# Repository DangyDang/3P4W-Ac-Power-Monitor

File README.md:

I dropped the project lol :( 
My firmware worked but it nothing compare to a dedicated IC for power monitoring.

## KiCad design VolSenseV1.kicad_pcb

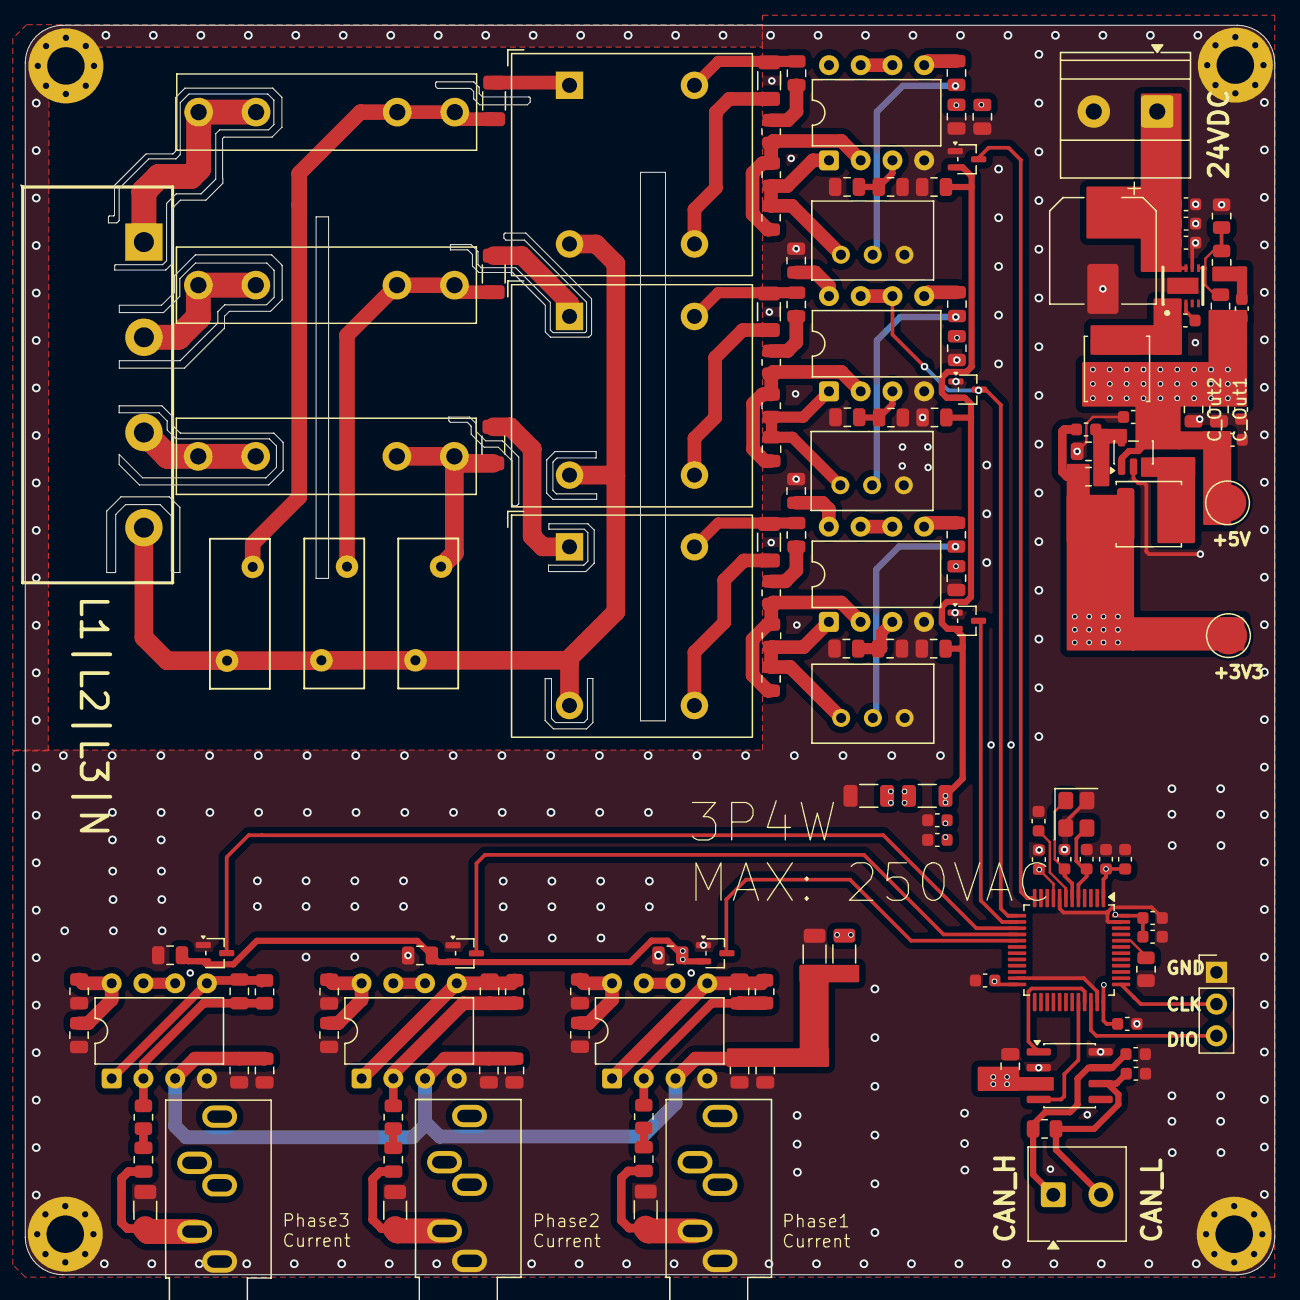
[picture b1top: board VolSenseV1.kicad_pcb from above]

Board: 4 copper layers, 100.0 x 100.0 mm, 148 parts (0 on the bottom side), 76 nets.

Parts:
C1, C2, C3, C4, C5, C6, C7, C8, C39, C43, C63: 100n; C_0603_1608Metric
C9, C10: 22p; C_0603_1608Metric
C11, C15, C19, C23, C28, C33: DNI; C_0805_2012Metric
C12, C13, C14, C16, C17, C18, C20, C21, C22, C24, C25, C26, C27, C29, C30, C31, C32, C34, C35, C36, C37, C44, C45, C47, C48, C50, C51, C57, C58, C59, C60, C61, C62: C; C_0805_2012Metric
C38: 100u; CP_Elec_8x6.2
C40: NC; C_0603_1608Metric
C41, C42: 10u; C_0603_1608Metric
C46, C49, C52, C53, C54, C55, C56: 100n; C_0805_2012Metric
C64, C65: 33pf; C_0603_1608Metric
C_FF1: 33p; C_0603_1608Metric
C_IN1, C_IN2: 4u7; C_0603_1608Metric
C_Out1, C_Out2: 33u; C_0805_2012Metric
C_boot1: 100nf; C_0603_1608Metric
Cin_HF1: 100n; C_0603_1608Metric
D1, D2, D3, D4, D5, D6: BAT54SW; SOT-323_SC-70
F1, F2, F3: Fuse; Fuseholder_Littelfuse_100_series_5x20mm
H1, H2, H3, H4: MountingHole_Pad; MountingHole_3mm_Pad_Via
J1: Conn_01x02; TerminalBlock_Phoenix_MKDS-1-2-3.81_1x02_P3.81mm_Horizontal
J2: Conn_01x03; PinHeader_1x03_P2.54mm_Vertical
J3, J4, J5: AudioJack4; Jack_3.5mm_CUI_SJ1-3535NG_Horizontal
J6: POWER INPUT; TerminalBlock_Phoenix_MKDS-1,5-2-5.08_1x02_P5.08mm_Horizont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
L1: 5u6; L_Sunlord_SWPA5020S
L2: 2u2; L_Sunlord_SWPA5020S
R1: 120; R_0805_2012Metric
R2, R3, R5, R6, R10, R11, R13, R15, R17, R19, R21, R23, R29: R; R_0805_2012Metric
R4, R7, R8, R9, R12, R27, R28: R; R_1206_3216Metric
R14, R18, R22: 820k; R_1206_3216Metric
R16, R20, R24: 100; R_1206_3216Metric
R25: 68k; R_0805_2012Metric
R26: 15k; R_0805_2012Metric
RV1, RV3, RV5: 275 VAC; RV_Disc_D12mm_W4.8mm_P7.5mm
RV2, RV4, RV6: R_Potentiometer; Potentiometer_Bourns_3299W_Vertical
R_FBB1: 19k1; R_0805_2012Metric
R_FBT1: 100k; R_0805_2012Metric
R_FF1: 1k; R_0805_2012Metric
TP1, TP2: TestPoint; TestPoint_Pad_D3.0mm
TR1, TR2, TR3: ZMPT101K; Transformer_Zeming_ZMPT101K
U1: STM32F103C8Tx; LQFP-48_7x7mm_P0.5mm
U2: TJA1051T; SOIC-8_3.9x4.9mm_P1.27mm
U3, U4, U5, U6, U8, U9: MCP6002-xP; DIP-8_W7.62mm
U7: KF7.62-4P; C707826_CONN-TH_KF7_62-4P
U10: LMR51450SDRRR; C6890985_WSON-12_L3_0-W3_0-P0_50-TL-EP-2
U11: TLV62569DBV; SOT-23-5
Y1: Crystal_GND24; Crystal_SMD_3225-4Pin_3.2x2.5mm

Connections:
+3V3: C1.1, C2.1, C3.1, C4.1, C5.1, C6.1, C7.1, C8.1, C40.1, C41.1, C57.2, C58.2, C59.2, C60.2, C61.2, C62.2, D1.2 (K), D2.2 (K), D3.2 (K), D4.2 (K), D5.2 (K), D6.2 (K), L2.2, R7.2, R25.1, R27.2, TP1.1, U1.1 (VBAT), U1.9 (VDDA), U1.24 (VDD), U1.36 (VDD), U1.48 (VDD)
+5V: C39.1, C42.1, C43.1, C44.2, C45.2, C46.1, C47.2, C48.2, C49.1, C50.2, C51.2, C52.1, C53.1, C54.1, C55.1, C56.1, C_FF1.1, C_Out1.1, C_Out2.1, L1.1, R_FBT1.1, TP2.1, U2.3 (VCC), U3.8 (V+), U4.8 (V+), U5.8 (V+), U6.8 (V+), U8.8 (V+), U9.8 (V+), U11.1 (EN), U11.4 (VIN)
/Power/Vin: C38.1, C_IN1.1, C_IN2.1, Cin_HF1.1, J6.1, U10.9 (EN), U10.10 (VIN), U10.11 (VIN), U10.12 (VIN)
CAN_H: C64.1, J1.1, R1.1, U2.7 (CANH)
CAN_L: C65.1, J1.2, R1.2, U2.6 (CANL)
CAN_RX: U1.32 (PA11), U2.4 (RXD)
CAN_TX: U1.33 (PA12), U2.1 (TXD)
CLK: J2.2, U1.37 (PA14)
DIO: J2.3, U1.34 (PA13)
GND: C1.2, C2.2, C3.2, C4.2, C5.2, C6.2, C7.2, C8.2, C9.1, C10.1, C13.1, C14.1, C17.1, C18.1, C21.1, C22.1, C26.1, C27.1, C31.1, C32.1, C36.1, C37.1, C38.2, C39.2, C41.2, C42.2, C43.2, C44.1, C45.1, C46.2, C47.1, C48.1, C49.2, C50.1, C51.1, C52.2, C53.2, C54.2, C55.2, C56.2, C57.1, C58.1, C59.1, C60.1, C61.1, C62.1, C63.1, C64.2, C65.2, C_IN1.2, C_IN2.2, C_Out1.2, C_Out2.2, Cin_HF1.2, D1.1 (A), D2.1 (A), D3.1 (A), D4.1 (A), D5.1 (A), D6.1 (A), H1.1, H2.1, H3.1, H4.1, J2.1, J3.S, J4.S, J5.S, J6.2, R4.2, R8.2, R9.1, R12.2, R26.2, R28.1, R29.2, RV2.3, RV4.3, RV6.3, R_FBB1.2, U1.8 (VSSA), U1.23 (VSS), U1.35 (VSS), U1.47 (VSS), U2.2 (GND), U2.8 (S), U3.4 (V-), U4.4 (V-), U5.4 (V-), U6.4 (V-), U8.4 (V-), U9.4 (V-), U10.8 (AGND), U10.13 (EP), U11.2 (GND), Y1.2 (G), Y1.4 (G)
L1: F1.1, U7.1
L2: F2.1, U7.2
L3: F3.1, U7.3
unnamed: C12.1, J3.T, R4.1
unnamed: C12.2, R3.1
unnamed: C16.1, J4.T, R8.1
unnamed: C16.2, R6.1
unnamed: C20.1, J5.T, R12.1
unnamed: C20.2, R11.1
unnamed: C23.2, R13.2, RV2.1, U6.1
unnamed: C24.1, R15.1
unnamed: C24.2, R16.2, TR1.4
unnamed: C25.2, RV2.2
unnamed: C28.2, R17.2, RV4.1, U8.1
unnamed: C29.1, R19.1
unnamed: C29.2, R20.2, TR2.4
unnamed: C30.2, RV4.2
unnamed: C33.2, R21.2, RV6.1, U9.1
unnamed: C34.1, R23.1
unnamed: C34.2, R24.2, TR3.4
unnamed: C35.2, RV6.2
unnamed: C_FF1.2, R_FF1.2
unnamed: C_boot1.2, L1.2, U10.1 (SW), U10.2 (SW), U10.3 (SW)
unnamed: F1.2, R14.1, RV1.1
unnamed: F2.2, R18.1, RV3.1
unnamed: F3.2, R22.1, RV5.1
unnamed: R14.2, TR1.1
unnamed: R16.1, TR1.3
unnamed: R18.2, TR2.1
unnamed: R20.1, TR2.3
unnamed: R22.2, TR3.1
unnamed: R24.1, TR3.3
unnamed: R29.1, U1.44 (BOOT0)
unnamed: C63.2, U1.7 (NRST)
unnamed: C9.2, U1.5 (PD0), Y1.3
unnamed: C10.2, U1.6 (PD1), Y1.1
unnamed: C11.1, R2.1, R3.2, U3.2 (-)
unnamed: C11.2, R2.2, U3.1, U3.5 (+)
unnamed: U3.6 (-), U3.7
unnamed: C15.1, R5.1, R6.2, U4.2 (-)
unnamed: C15.2, R5.2, U4.1, U4.5 (+)
unnamed: U4.6 (-), U4.7
unnamed: C19.1, R10.1, R11.2, U5.2 (-)
unnamed: C19.2, R10.2, U5.1, U5.5 (+)
unnamed: U5.6 (-), U5.7
unnamed: C23.1, R13.1, R15.2, U6.2 (-)
unnamed: C25.1, U6.5 (+)
unnamed: U6.6 (-), U6.7
unnamed: C28.1, R17.1, R19.2, U8.2 (-)
unnamed: C30.1, U8.5 (+)
unnamed: C33.1, R21.1, R23.2, U9.2 (-)
unnamed: C35.1, U9.5 (+)
unnamed: U9.6 (-), U9.7
unnamed: C_boot1.1, U10.4 (BOOT)
unnamed: R_FBB1.1, R_FBT1.2, R_FF1.1, U10.7 (FB)
unnamed: C40.2, R25.2, R26.1, U11.5 (FB)
unnamed: L2.1, U11.3 (SW)
Neutral: RV1.2, RV3.2, RV5.2, TR1.2, TR2.2, TR3.2, U7.4
OpAmp Vref ~ 1.65: C26.2, C27.2, C31.2, C32.2, C36.2, C37.2, R27.1, R28.2, U6.3 (+), U8.3 (+), U9.3 (+)
OpAmp Vref ~ 1.65 (1): C13.2, C14.2, C17.2, C18.2, C21.2, C22.2, R7.1, R9.2, U3.3 (+), U4.3 (+), U5.3 (+)
Phase 1 Voltage: D2.3 (COM), U1.12 (PA2)
Phase 1 current: D5.3 (COM), U1.17 (PA7)
Phase 2 Voltage: D1.3 (COM), U1.13 (PA3), U8.6 (-), U8.7
Phase 2 current: D6.3 (COM), U1.15 (PA5)
Phase 3 Voltage: D3.3 (COM), U1.14 (PA4)
Phase 3 current: D4.3 (COM), U1.16 (PA6)
